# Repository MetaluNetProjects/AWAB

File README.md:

# AWAB

Design files for Véronique Béland's AWAB project.

Fraise firmware for :
- galvanic skin response multipoint sensor 
- FSR sensor 
- 2 leds 
- 1 12V pwm channel (12V led dimmer).

PureData driver patch & test network client.

metalu.net 2016

-----
##Install :

- pd 0.46-7 minimum
- deken (if not already installed : https://github.com/pure-data/deken )
- pd externals (through deken : Pd/Help/Find externals)
	-	zexy 2.2.6 
	-	moonlib 
	-	hcs 
	-	ggee
	-	comport 
- Fraise : extract https://github.com/MetaluNet/Fraise/archive/master.zip into ~/pd-externals.  

On Linux, you may need to add your user to the dialout group, 
to have read/write permissions on the USB device /dev/ttyACM0. Just do :   
`sudo adduser [your_username] dialout`

then logout and re-login.

-----
##Running
1) launch : `pd 0main.pd`
   if you want to specify network tcp port (intead of default 45451) :
   `pd -send "NETWORK_PORT [port]" -open 0main.pd`

2) for testing : `pd 0testClient.pd` ; connect ; try commands.

-----
##Network communication

port : 45451 tcp

commands :

- `select A(int:0 to 15) B(int:0 to 15)` : select mesure terminals pair

- `getMesure` : ask current mesure.   
  Returns : m M(float) ; wait 200ms min since last `select`.

- `handCapture` : query for all 35 hand mesurements.   
  Returns : `hc m1 m2 (...) m35` where m1-35 are floats

- `getWeight` : query weight mesurement.  
  Returns : `w weight(float)`

- `light P(float:0.0 to 1.0) T(float:milliseconds)` : set light1 power ; transition time parameter T is optionnal

- `light2 P T` : set light2 power. T is optionnal.

- `leds LED1(bool:0/1) LED2(bool:0/1)` : set leds state.
 
- `clearOffset` : clear mesure offset.

- `clearWeightOffset` : clear weight mesure offset.

- `progress P(int:0 to 10)` : switch progress bar leds 1 to P on.

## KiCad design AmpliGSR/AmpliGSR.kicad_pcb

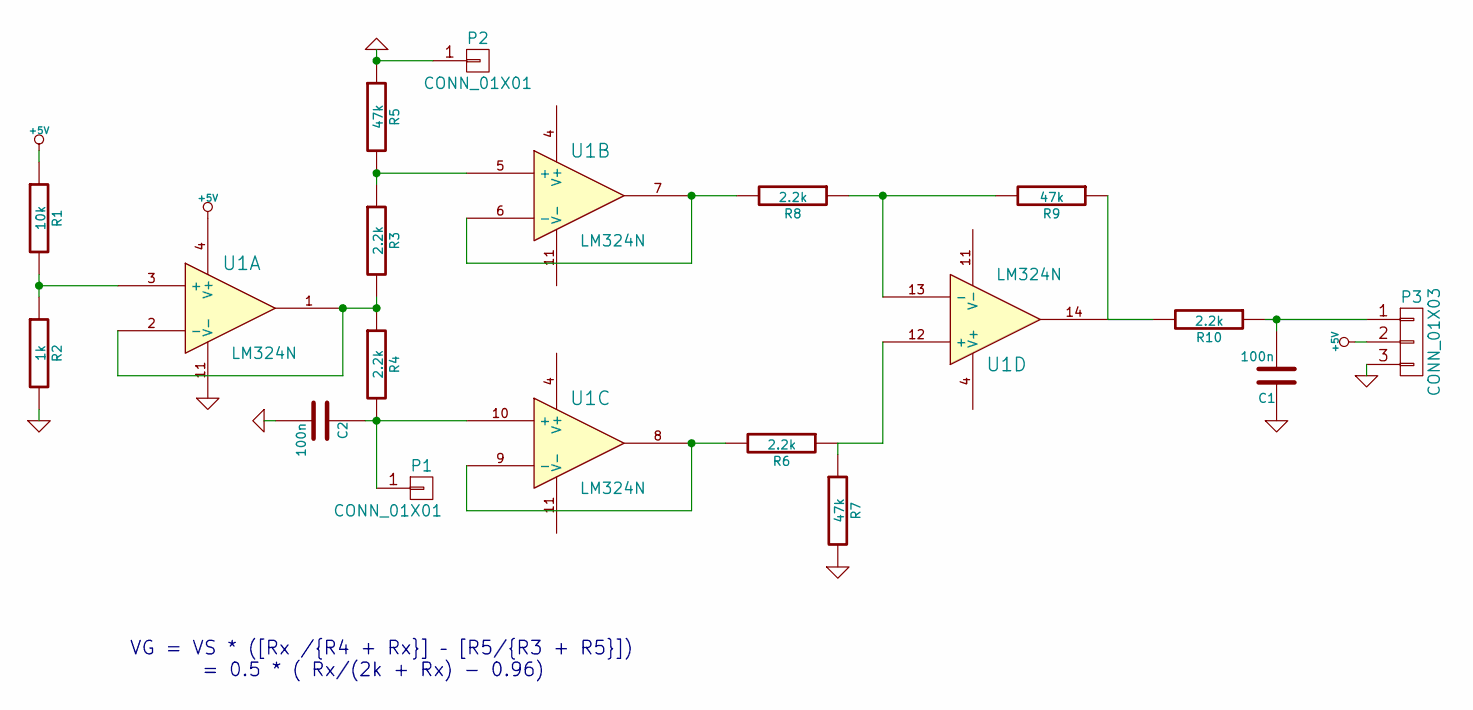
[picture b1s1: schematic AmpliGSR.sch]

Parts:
C1, C2: 100n; C_Rect_L7_W2_P5
P1, P2: CONN_01X01; 1pin
P3: CONN_01X03; Molex_KK_6410-03
R1: 10k; Resistor_Horizontal_RM7mm
R2: 1k; Resistor_Horizontal_RM7mm
R3, R4, R6, R8, R10: 2.2k; Resistor_Horizontal_RM7mm
R5, R7, R9: 47k; Resistor_Horizontal_RM7mm
U1: LM324N; DIP-14_W7.62mm_LongPads

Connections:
+5V: P3.2, R1.1, U1.4 (V+)
GND: C1.1, C2.2, P2.1, P3.3, R2.2, R5.1, R7.2, U1.11 (V-); also elsewhere on the board
unnamed 2: C1.2, P3.1, R10.1; also elsewhere on the board
unnamed: C2.1, P1.1, R4.2, U1.10 (+)
unnamed: R1.2, R2.1, U1.3 (+)
unnamed: R3.1, R5.2, U1.5 (+)
unnamed: R3.2, R4.1, U1.1, U1.2 (-)
unnamed: R6.1, R7.1, U1.12 (+)
unnamed: R6.2, U1.8, U1.9 (-)
unnamed: R8.1, R9.2, U1.13 (-)
unnamed: R8.2, U1.6 (-), U1.7
unnamed: R9.1, R10.2, U1.14

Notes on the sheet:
VG = VS * ([Rx /{R4 + Rx}] – [R5/{R3 + R5}]) = 0.5 * ( Rx/(2k + Rx) - 0.96)

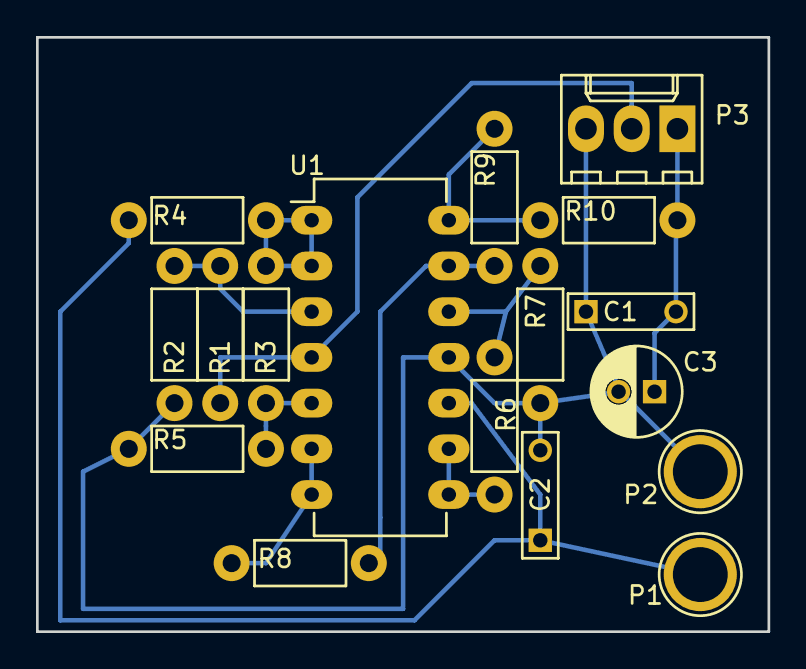
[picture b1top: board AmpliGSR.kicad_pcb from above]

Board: 2 copper layers, 40.6 x 33.0 mm, 17 parts (0 on the bottom side), 12 nets.

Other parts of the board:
C3: 10u; C_Radial_D5_L11_P2

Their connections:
GND: C3.2; also elsewhere on the board
unnamed 2: C3.1; also elsewhere on the board

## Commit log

2016-07-05 add project files and update README
2016-07-05 update README and clean
2016-09-06 update ampli schematic & pcb
2016-09-06 add progress-led-bar fruit
2016-09-06 add calibration-interpolator for weight estimation
2016-09-06 update adc fruit for including a 2nd PWM channel ; change channels swaping period to 13ms
2016-09-06 update main patch and testClient patch to reflect latest changes (weight estimation and light2 PWM channel
2016-09-06 add doc about installing and about network commands in README
2016-09-06 save last test sessions
2016-09-08 update ledbar for final circuit
2016-09-08 keep trace of weight calibration tables
2016-09-08 save Sessions.txt
2016-09-09 minor clean
2016-09-19 Complete README by adding progress command...
2016-09-29 Add hx711 driver for better weight sensing (than FSR)
2016-09-29 Update patch about weight sensing
2016-09-29 Add mention in README about redirecting network port
2016-09-29 Correct last change
2016-09-30 fix weight sent to network
2016-09-30 min weight is now 0 (no more negative)
2016-10-10 better measure computing
2017-02-07 keep pd patch responsible of the measure delay
